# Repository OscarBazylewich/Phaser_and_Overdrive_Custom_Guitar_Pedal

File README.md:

# Phaser and Overdrive Guitar Pedal

This project tries to make better equivalents of guitar pedals that many guitar players use, for example the MXR Phase 90 and the BOSS OD-1. For this, the project uses new methods of analog circuit design and PCB design. For the overdrive, the project also uses some circuit methods from the Ibanez Tube Screamer.

This repository contains these items:

- An LTspice schematic, with the third-party TL072 model that the schematic uses.
- A KiCad project. In this project, the two effects, the power supply and two footswitches are on one 4-layer PCB. The PCB has the correct dimensions for a Hammond 1590BB enclosure.

## Features

- A JFET phaser with four all-pass stages (Rate, Depth). An LFO on the PCB modulates the phaser.
- An overdrive with diode clipping, of the OD-1 and Tube Screamer type (Gain, Tone).
- An input buffer, and one DPDT footswitch for each effect. The signal goes through the phaser first.
- One DC jack supplies the power. The PCB makes the ±4.5 V rails. It also has reverse-polarity protection and surge protection.
- An 85.5 mm × 110.75 mm 4-layer PCB, with TVS protection on the two audio jacks.

## Hardware

### Signal flow

```mermaid
flowchart LR
    IN["Input jack J3"] --> BUF["Input buffer<br/>U5A"]
    BUF --> S1["Phaser footswitch<br/>S1"]
    S1 --> PH["Phaser<br/>4 all-pass stages"]
    S1 -- "phaser off" --> S2["Overdrive footswitch<br/>S2"]
    PH --> S2
    S2 --> OD["Overdrive<br/>gain, clipping, tone"]
    S2 -- "overdrive off" --> OUT["Output jack J2"]
    OD --> OUT
    LFO["Triangle LFO<br/>U5C, U5D"] --> PH
```

### Primary parts

| Part | Function |
| --- | --- |
| U1 TPS560430 buck converter | DC input to +5.5 V |
| U2 LM2662 charge pump | +5.5 V to −5.5 V |
| U3 TPS72301, U4 TPS7E82 LDOs | −4.5 V and +4.5 V rails |
| U5–U7 TL074 quad op-amps | Buffers, LFO, phaser, overdrive |
| Q1–Q4 J113 JFETs | Voltage-controlled resistors in the phaser |
| D1 CUS520 Schottky, D2–D4 20 V TVS | Reverse-polarity, surge and ESD protection |
| D5–D8 1N4148 | Overdrive clipping diodes |
| VR1–VR4 PTV09A potentiometers, RV1/RV2 3386P trimmers | Controls (refer to the next table) |
| S1, S2 SF12011F DPDT footswitches | Phaser and overdrive on/off |
| J1 2.1 × 5.5 mm DC jack, J2/J3 MJ-63022A 6.35 mm jacks | Power, output, input |

### Controls

| Control | Ref | Value | Function |
| --- | --- | --- | --- |
| Rate | VR1 | 1 MΩ linear | LFO frequency |
| Depth | VR2 | 1 MΩ linear | Level of the phase-shifted signal in the mixed output |
| Tone | VR3 | 20 kΩ log | Tone control (active filter) |
| Gain | VR4 | 1 MΩ log | Overdrive feedback resistance |
| LFO offset trimmer | RV1 | 500 kΩ | LFO DC level (J113 bias) |
| LFO hysteresis trimmer | RV2 | 220 kΩ | LFO amplitude and frequency |

## Circuit

The sections that follow use the KiCad reference designators. The LTspice schematic uses different reference designators.

The LTspice schematic has the same topology and the same values as the KiCad schematic, with these differences:

- All the potentiometers are linear.
- The Tone potentiometer is 1 MΩ (KiCad: 20 kΩ).
- The clipping diodes are 1N4007 (KiCad: 1N4148).
- There are no footswitches.
- Ideal ±4.5 V sources supply the power.
- The same input signal goes to the phaser and to the overdrive. The phaser and the overdrive have different outputs.

### Power supply

- The KiCad schematic gives 9–18 V as the range for the DC input. D1 (Schottky, in series) gives reverse-polarity protection. D2 (20 V TVS) sends surges to ground.
- U1 (buck converter) makes +5.5 V. U2 (charge pump) changes this voltage to an unregulated −5.5 V.
- U4 and U3 (LDOs) decrease these voltages to ±4.5 V. Each TL074 has 100 nF decoupling capacitance on each rail.

### Input buffer and footswitches

- C14 (1 µF) connects the tip of the input jack to U5A through AC coupling. U5A is a voltage follower.
- R9 (1 MΩ) sets the input impedance and the DC bias. D4 gives ESD protection on the tip.
- Each footswitch is a DPDT selector. It sends the signal through the effect, or it bypasses the effect.
- NC_1 and NC_2 are connected together. Thus, when an effect is off, the footswitch bypasses that effect.
- When the two effects are off, U5A stays in the signal path.

### LFO

- U5C is a Schmitt trigger. The output of U5C charges and discharges C16 (4.7 µF) through the Rate potentiometer.
- RV2 sets the hysteresis. The LTspice notes give an LFO frequency range of approximately 0.185 Hz to 12.2 Hz.
- U5D amplifies the voltage on C16 and makes the `TriangleOut` signal. `TriangleOut` goes to the gates of all four JFETs (test pad TP3).
- RV1 sets the DC offset of `TriangleOut`. This offset sets the bias of the JFETs. The LTspice notes give a J113 cut-off voltage of −0.5 V to −3.0 V.

### Phaser

- U6A is the phaser buffer. The output of U6A goes to the all-pass stages and to the dry path.
- There are four all-pass stages (U7A–U7D). Each stage has a J113 JFET across a 56 kΩ resistor to ground.
- When the LFO changes the gate voltage, the resistance of the JFET changes. Thus, the phase-shift frequency of the stage also changes.
- U6B adds the phase-shifted signal from the Depth potentiometer to the dry signal. At some frequencies, the two signals are out of phase. At these frequencies, phase cancellation occurs. This phase cancellation makes the notches.
- The LTspice notes show the two notches at 53.5 Hz and 311.9 Hz (R = 56 kΩ, C = 22 nF).
- When current flows through the JFETs, the frequencies of the notches increase. This occurs because the JFETs decrease the total resistance across R.

### Overdrive

- U6C is a non-inverting gain stage. R29 (56 kΩ) plus the Gain potentiometer is the feedback resistance. C28 (82 pF) and two anti-parallel diode pairs (D5–D8) are across this resistance.
- The mid-band gain is approximately 6.6× to 107×. The lower corner frequency of the amplified band is approximately 723 Hz (R30 10 kΩ, C30 22 nF).
- When the signal voltage is more than the total forward voltage of two diodes, current flows through the diodes. The diodes then give soft clipping of the signal in the feedback loop.
- The signal then goes through a passive RC low-pass filter (723 Hz) to the tone stage U6D. The LTspice schematic identifies this tone stage as an active high-pass filter (3.288 kHz at wiper = 1).

## How to start

These items are necessary:

- KiCad 10.0 or a newer version.
- LTspice.
- An LTspice potentiometer model. You must supply this model.

The LTspice schematic loads `potentiometer.sub`. This repository does **not** include this file.

### How to import third-party models into LTspice

1. Download the .sub and .asy files from the `LTSpice/3rdParty/` folder.
2. Put the files in your local LTspice folder:
   - Put the .sub files in the `sub` folder.
   - Put the TL072 .asy file in the `sym/OpAmps/` folder, because the LTspice schematic identifies the op-amp as `OpAmps\TL072`.
   - Put all other .asy files in the `sym` folder.
3. Put the files of your potentiometer model in the folders of step 2.
4. Open `LTSpice/Schematic.asc`.
5. Start the simulation (a 15 s `.tran` with a 100 mV, 100 Hz test tone).
6. Use the probe to show the waveforms of `InputSignal`, `TriangleOut`, `SignalOutPhaser` and `SignalOutOD`.
7. To show the frequency response, do these steps:
   1. Change the `.ac` comment line to a SPICE directive.
   2. Change the `.tran` directive to a comment.
   3. Start the simulation again.

**Note:** When you update LTspice, LTspice can delete the third-party models.

To keep your third-party models, do these steps:

1. Keep a copy of all your third-party .sub and .asy files in a different folder (not in your local LTspice folder).
2. After you update LTspice, manually copy these files into the same folders as in step 2 of "How to import third-party models into LTspice".

### How to import third-party libraries into KiCad

You can open `KiCAD/GuitarPedalV4.kicad_pro` in KiCad 10 without these libraries. This is possible because the KiCad schematic and the PCB file contain all the symbols and footprints. These libraries are necessary only when you edit parts.

1. Extract the two ZIP files in `KiCAD/Libraries/` into a folder that you select.
2. To import the symbols, do these steps:
   1. Open the symbol editor.
   2. Click the **Preferences** menu.
   3. Select **Manage Symbol Libraries**.
   4. Click the folder icon.
   5. Navigate to a folder that contains .kicad_sym files.
   6. Import the .kicad_sym files in this folder.
   7. Keep each file name as its nickname, because the KiCad schematic uses these names.
   8. If other folders contain .kicad_sym files, do steps 4 to 7 again for each of these folders.

   **Note:** The KiCad project uses these .kicad_sym files: the five `1_...` files, `Chassis` (in `Chassis.pretty/`) and `SamacSys_Parts`.
3. To import the footprints, do these steps:
   1. Open the footprint editor.
   2. Click the **Preferences** menu.
   3. Select **Manage Footprint Libraries**.
   4. Click the folder icon.
   5. Add the `Chassis.pretty` and `SamacSys_Parts.pretty` folders. Each footprint library is a folder, not one .kicad_mod file.
4. If KiCad does not show the 3D models of the custom parts, change the paths of these 3D models:
   1. For each footprint of a custom part, navigate to **Footprint Properties > 3D Models**.
   2. Change the path to the related STEP file in the extracted `SamacSys_Parts.3dshapes/` or `Chassis.pretty/3D Files/` folder.

   **Note:** These 3D models use absolute paths on the computer of the designer.

## Repository structure

```text
.
├── KiCAD/
│   ├── GuitarPedalV4.kicad_pro      # KiCad 10 project
│   ├── GuitarPedalV4.kicad_sch      # Root sheet
│   ├── PowerSupply.kicad_sch        # Power supply
│   ├── Analog.kicad_sch             # Buffer, LFO, phaser, footswitches, jacks
│   ├── Overdrive.kicad_sch          # Overdrive sub-sheet
│   ├── GuitarPedalV4.kicad_pcb      # 4-layer PCB
│   └── Libraries/                   # ZIP files of the DIY and SamacSys libraries
├── LTSpice/
│   ├── Schematic.asc                # Full circuit with LTspice notes
│   └── 3rdParty/                    # TL072 model and symbol
├── LICENSE
└── README.md
```

## Simulation examples

## Credits

- Oscar Bazylewich did the circuit design, the simulation and the PCB layout.
- This project uses the MXR Phase 90, the BOSS OD-1 and the Ibanez Tube Screamer as examples.
- TL072 LTspice model: third-party macromodel (`tl072.sub`, from PARTS release 4.01).
- SamacSys supplied the KiCad symbols, footprints and 3D models of the J113, MJ-63022A, PTV09A, 3386P and SF12011F parts.

## License

The license of this project is the GNU General Public License v3.0. Refer to [LICENSE](LICENSE).

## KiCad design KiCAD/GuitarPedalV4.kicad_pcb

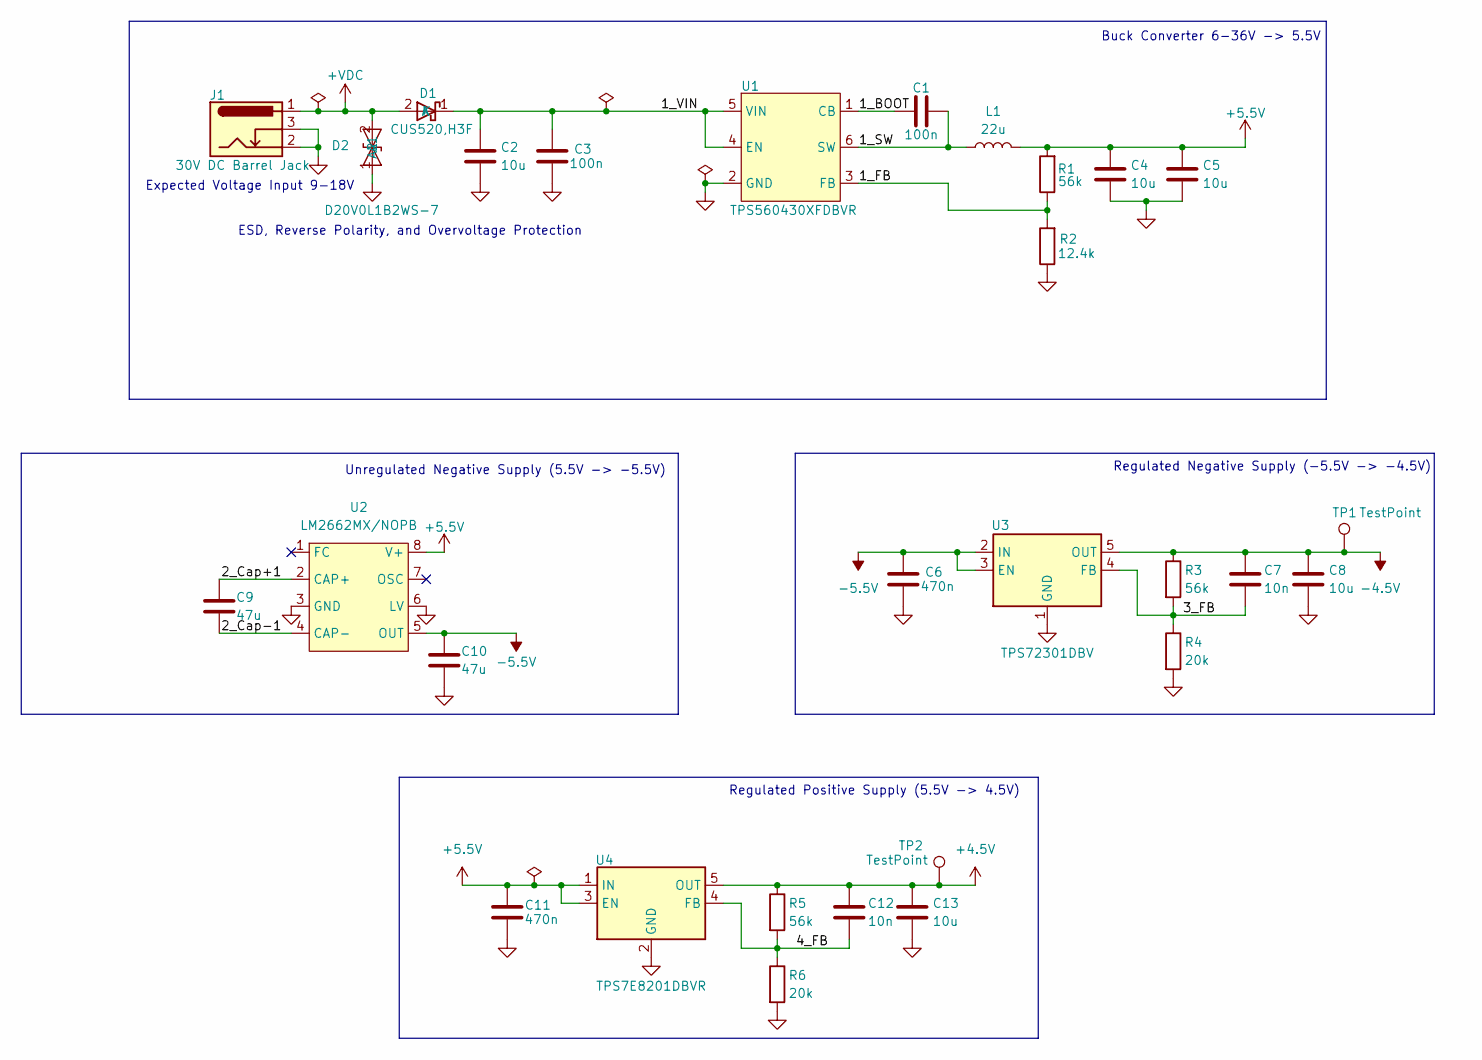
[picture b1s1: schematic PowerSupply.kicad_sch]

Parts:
C1, C3: 100n; C_0603_1608Metric_Pad1.08x0.95mm_HandSolder; Manufacturer Part Number C1608X5R1H104K080AA
C2, C4, C5, C8, C13: 10u; C_0805_2012Metric_Pad1.18x1.45mm_HandSolder; Manufacturer Part Number C2012X5R1H106K125AC
C6, C11: 470n; C_0603_1608Metric_Pad1.08x0.95mm_HandSolder; Manufacturer Part Number CGA3E1X7R1V474K080AC
C7, C12: 10n; C_0603_1608Metric_Pad1.08x0.95mm_HandSolder; Manufacturer Part Number CGA3E2X7R1H103K080AA
C9, C10: 47u; C_1206_3216Metric_Pad1.33x1.80mm_HandSolder; Manufacturer Part Number C3216X5R1E476M160AC
D1: CUS520,H3F; D_SOD-323_HandSoldering; Manufacturer Part Number CUS520,H3F
D2: D20V0L1B2WS-7; D_SOD-323_HandSoldering; Manufacturer Part Number D20V0L1B2WS-7
J1: 30V DC Barrel Jack; BarrelJack_GCT_DCJ200-10-A_Horizontal; Manufacturer Part Number 694106301002
L1: 22u; L_0805_2012Metric_Pad1.05x1.20mm_HandSolder; Manufacturer Part Number MLZ2012P220WTD25
R1, R3, R5: 56k; R_0603_1608Metric_Pad0.98x0.95mm_HandSolder; Manufacturer Part Number CRCW060356K0FKEA
R2: 12.4k; R_0603_1608Metric_Pad0.98x0.95mm_HandSolder; Manufacturer Part Number CRCW060312K4FKEA
R4, R6: 20k; R_0603_1608Metric_Pad0.98x0.95mm_HandSolder; Manufacturer Part Number CRCW060320K0FKEC
TP1, TP2: TestPoint; TestPoint_Pad_1.0x1.0mm
U1: TPS560430XFDBVR; SOT-23-6; Manufacturer Part Number TPS560430XFDBVR
U2: LM2662MX/NOPB; SOIC-8_3.9x4.9mm_P1.27mm; Manufacturer Part Number LM2662MX/NOPB
U3: TPS72301DBV; SOT-23-5_HandSoldering; Manufacturer Part Number TPS72301DBVRG4
U4: TPS7E8201DBVR; SOT-23-5_HandSoldering; Manufacturer Part Number TPS7E8201DBVR

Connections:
+4.5V: C12.1, C13.1, R5.1, TP2.1 (1_1), U4.5 (OUT); also elsewhere on the board
+5.5V: C4.1, C5.1, C11.2, L1.2, R1.2, U2.8 (V+), U4.1 (IN), U4.3 (EN)
+VDC: D1.2 (A), D2.2 (A2), J1.1
-4.5V: C7.1, C8.1, R3.1, TP1.1 (1_1), U3.5 (OUT); also elsewhere on the board
-5.5V: C6.2, C10.1, U2.5 (OUT), U3.2 (IN), U3.3 (EN)
/Power Supply Section/1_BOOT: C1.2, U1.1 (CB)
/Power Supply Section/1_FB: R1.1, R2.2, U1.3 (FB)
/Power Supply Section/1_SW: C1.1, L1.1, U1.6 (SW)
/Power Supply Section/1_VIN: C2.1, C3.2, D1.1 (K), U1.4 (EN), U1.5 (VIN)
/Power Supply Section/2_Cap+1: C9.1, U2.2 (CAP+)
/Power Supply Section/2_Cap-1: C9.2, U2.4 (CAP-)
/Power Supply Section/3_FB: C7.2, R3.2, R4.1, U3.4 (FB)
/Power Supply Section/4_FB: C12.2, R5.2, R6.1, U4.4 (FB)
GND: C2.2, C3.1, C4.2, C5.2, C6.1, C8.2, C10.2, C11.1, C13.2, D2.1 (A1), J1.2, J1.3, R2.1, R4.2, R6.2, U1.2 (GND), U2.3 (GND), U2.6 (LV), U3.1 (GND), U4.2 (GND); also elsewhere on the board

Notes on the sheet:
Regulated Negative Supply (-5.5V -> -4.5V)
ESD, Reverse Polarity, and Overvoltage Protection
Regulated Positive Supply (5.5V -> 4.5V)
Unregulated Negative Supply (5.5V -> -5.5V)
Expected Voltage Input 9-18V
Buck Converter 6-36V -> 5.5V

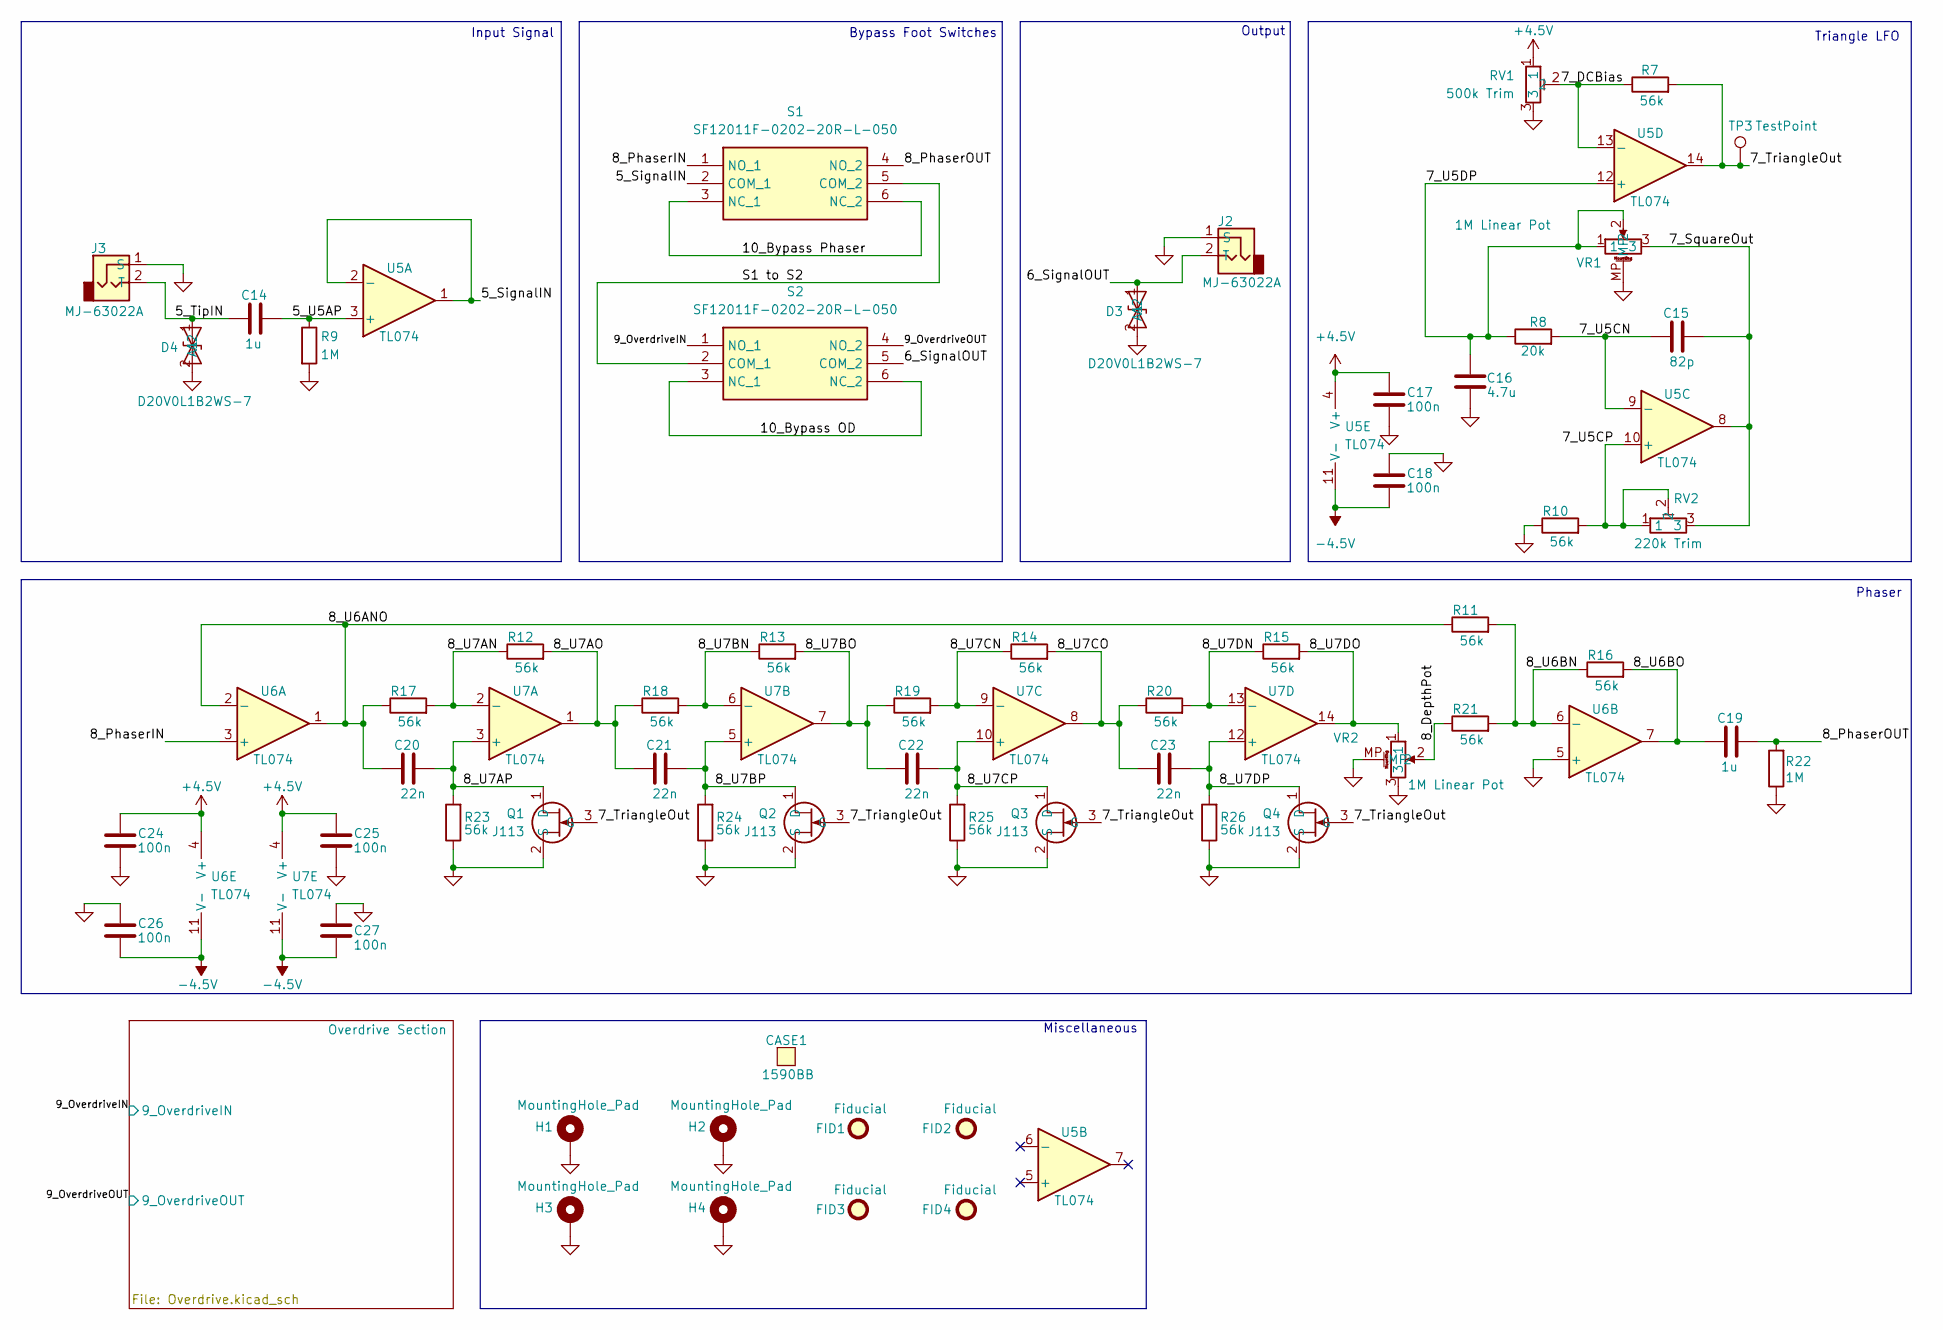
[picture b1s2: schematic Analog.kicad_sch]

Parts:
C14, C19: 1u; C_Rect_L7.2mm_W4.5mm_P5.00mm_FKS2_FKP2_MKS2_MKP2; Manufacturer Part Number B32529C0105J189
C15: 82p; C_Disc_D3.8mm_W2.6mm_P2.50mm; Manufacturer Part Number K820J15C0GF5TL2
C16: 4.7u; C_Rect_L18.0mm_W7.0mm_P15.00mm_FKS3_FKP3; Manufacturer Part Number B32522C0475J000
C17, C18, C24, C25, C26, C27: 100n; C_0603_1608Metric_Pad1.08x0.95mm_HandSolder; Manufacturer Part Number C1608X5R1H104K080AA
C20, C21, C22, C23: 22n; C_Rect_L7.2mm_W2.5mm_P5.00mm_FKS2_FKP2_MKS2_MKP2; Manufacturer Part Number B32529C1223J289
CASE1: 1590BB; Manufacturer Part Number 1590BB
D3, D4: D20V0L1B2WS-7; D_SOD-323_HandSoldering; Manufacturer Part Number D20V0L1B2WS-7
FID1, FID2, FID3, FID4: Fiducial
H1, H2, H3, H4: MountingHole_Pad; MountingHole_3.2mm_M3_Pad
J2, J3: MJ-63022A; MJ63022A; Manufacturer Part Number MJ-63022A
Q1, Q2, Q3, Q4: J113; 2N3904BU; Manufacturer Part Number J113
R7, R10, R11, R12, R13, R14, R15, R16, R17, R18, R19, R20, R21, R23, R24, R25, R26: 56k; R_0603_1608Metric_Pad0.98x0.95mm_HandSolder; Manufacturer Part Number CRCW060356K0FKEA
R8: 20k; R_0603_1608Metric_Pad0.98x0.95mm_HandSolder; Manufacturer Part Number CRCW060320K0FKEC
R9, R22: 1M; R_0603_1608Metric_Pad0.98x0.95mm_HandSolder; Manufacturer Part Number CRCW06031M00FKEA
RV1: 500k Trim; 3386P1504LF; Manufacturer Part Number 3386P-1-504LF
RV2: 220k Trim; 3386P1504LF; Manufacturer Part Number 3386P-1-224LF
S1, S2: SF12011F-0202-20R-L-050; SF12011F020220RM050; Manufacturer Part Number SF12011F-0202-20R-L-050
TP3: TestPoint; TestPoint_Pad_1.0x1.0mm
U5, U6, U7: TL074; SOIC-14_3.9x8.7mm_P1.27mm; Manufacturer Part Number TL074HIDR
VR1, VR2: 1M Linear Pot; PTV09A4025FA105; Manufacturer Part Number PTV09A-4020F-B105

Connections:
+4.5V: C17.2, C24.2, C25.2, RV1.1, U5.4 (V+), U6.4 (V+), U7.4 (V+); also elsewhere on the board
-4.5V: C18.1, C26.1, C27.1, U5.11 (V-), U6.11 (V-), U7.11 (V-); also elsewhere on the board
/Analog Section/5_SignalIN: S1.2 (COM_1), U5.1, U5.2 (-)
/Analog Section/5_TipIN: C14.1, D4.1 (A1), J3.2 (T)
/Analog Section/5_U5AP: C14.2, R9.1, U5.3 (+)
/Analog Section/6_SignalOUT: D3.1 (A1), J2.2 (T), S2.5 (COM_2)
/Analog Section/7_DCBias: R7.1, RV1.2, U5.13 (-)
/Analog Section/7_SquareOut: C15.2, RV2.3, U5.8, VR1.3
/Analog Section/7_TriangleOut: Q1.3 (G), Q2.3 (G), Q3.3 (G), Q4.3 (G), R7.2, TP3.1 (1_1), U5.14
/Analog Section/7_U5CN: C15.1, R8.2, U5.9 (-)
/Analog Section/7_U5CP: R10.2, RV2.1, RV2.2, U5.10 (+)
/Analog Section/7_U5DP: C16.2, R8.1, U5.12 (+), VR1.1, VR1.2
/Analog Section/8_DepthPot: R21.1, VR2.2
/Analog Section/8_PhaserIN: S1.1 (NO_1), U6.3 (+)
/Analog Section/8_PhaserOUT: C19.2, R22.2, S1.4 (NO_2)
/Analog Section/8_U6ANO: C20.1, R11.1, R17.1, U6.1, U6.2 (-)
/Analog Section/8_U6BN: R11.2, R16.1, R21.2, U6.6 (-)
/Analog Section/8_U6BO: C19.1, R16.2, U6.7
/Analog Section/8_U7AN: R12.1, R17.2, U7.2 (-)
/Analog Section/8_U7AO: C21.1, R12.2, R18.1, U7.1
/Analog Section/8_U7AP: C20.2, Q1.1 (D), R23.2, U7.3 (+)
/Analog Section/8_U7BN: R13.1, R18.2, U7.6 (-)
/Analog Section/8_U7BO: C22.1, R13.2, R19.1, U7.7
/Analog Section/8_U7BP: C21.2, Q2.1 (D), R24.2, U7.5 (+)
/Analog Section/8_U7CN: R14.1, R19.2, U7.9 (-)
/Analog Section/8_U7CO: C23.1, R14.2, R20.1, U7.8
/Analog Section/8_U7CP: C22.2, Q3.1 (D), R25.2, U7.10 (+)
/Analog Section/8_U7DN: R15.1, R20.2, U7.13 (-)
/Analog Section/8_U7DO: R15.2, U7.14, VR2.1
/Analog Section/8_U7DP: C23.2, Q4.1 (D), R26.2, U7.12 (+)
/Analog Section/9_OverdriveIN: S2.1 (NO_1); also elsewhere on the board
/Analog Section/9_OverdriveOUT: S2.4 (NO_2); also elsewhere on the board
/Analog Section/10_Bypass OD: S2.3 (NC_1), S2.6 (NC_2)
/Analog Section/10_Bypass Phaser: S1.3 (NC_1), S1.6 (NC_2)
/Analog Section/S1 to S2: S1.5 (COM_2), S2.2 (COM_1)
GND: C16.1, C17.1, C18.2, C24.1, C25.1, C26.2, C27.2, D3.2 (A2), D4.2 (A2), H1.1 (1_1), H2.1 (1_1), H3.1 (1_1), H4.1 (1_1), J2.1 (S), J3.1 (S), Q1.2 (S), Q2.2 (S), Q3.2 (S), Q4.2 (S), R9.2, R10.1, R22.1, R23.1, R24.1, R25.1, R26.1, RV1.3, U6.5 (+), VR1.MP, VR2.3, VR2.MP; also elsewhere on the board

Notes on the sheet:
Phaser
Miscellaneous
Output
Bypass Foot Switches
Input Signal
Triangle LFO

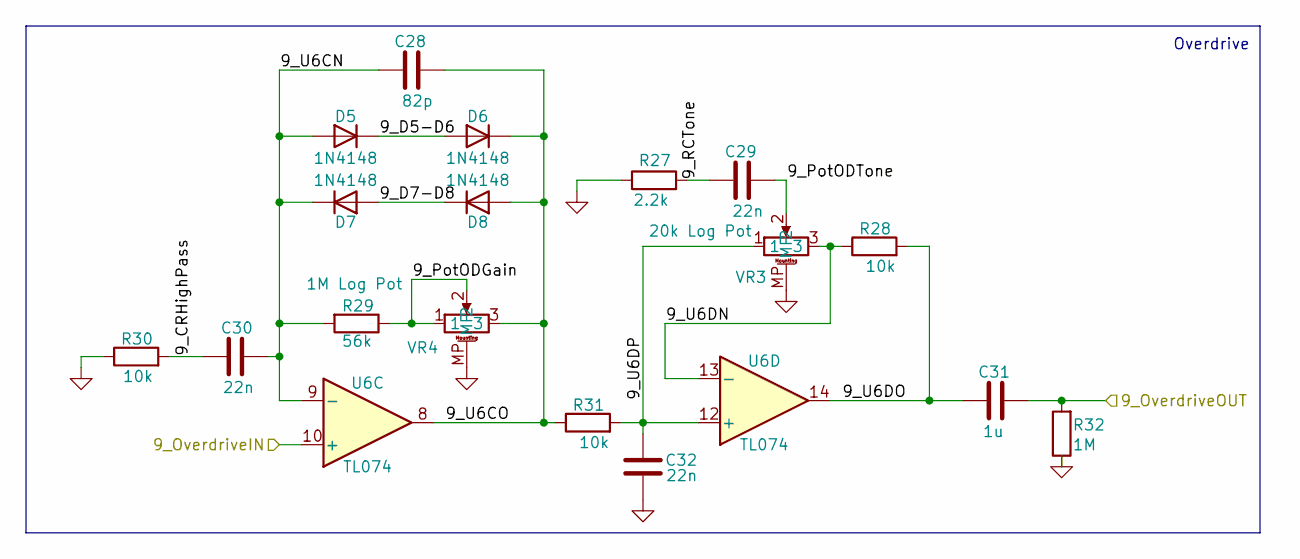
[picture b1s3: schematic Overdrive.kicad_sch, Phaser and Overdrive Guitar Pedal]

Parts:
C28: 82p; C_Disc_D3.8mm_W2.6mm_P2.50mm; Manufacturer Part Number K820J15C0GF5TL2
C29, C30, C32: 22n; C_Rect_L7.2mm_W2.5mm_P5.00mm_FKS2_FKP2_MKS2_MKP2; Manufacturer Part Number B32529C1223J289
C31: 1u; C_Rect_L7.2mm_W4.5mm_P5.00mm_FKS2_FKP2_MKS2_MKP2; Manufacturer Part Number B32529C0105J189
D5, D6, D7, D8: 1N4148; D_DO-35_SOD27_P7.62mm_Horizontal; Manufacturer Part Number 1N4148
R27: 2.2k; R_0603_1608Metric_Pad0.98x0.95mm_HandSolder; Manufacturer Part Number CRCW06032K20FKEA
R28, R30, R31: 10k; R_0603_1608Metric_Pad0.98x0.95mm_HandSolder; Manufacturer Part Number CRCW060310K0FKEA
R29: 56k; R_0603_1608Metric_Pad0.98x0.95mm_HandSolder; Manufacturer Part Number CRCW060356K0FKEA
R32: 1M; R_0603_1608Metric_Pad0.98x0.95mm_HandSolder; Manufacturer Part Number CRCW06031M00FKEA
U6: TL074; SOIC-14_3.9x8.7mm_P1.27mm; Manufacturer Part Number TL074HIDR
VR3: 20k Log Pot; PTV09A4025FA105; Manufacturer Part Number PTV09A-4025F-A203
VR4: 1M Log Pot; PTV09A4025FA105; Manufacturer Part Number PTV09A-4025F-A105

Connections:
/Analog Section/9_OverdriveIN: U6.10 (+); also elsewhere on the board
/Analog Section/9_OverdriveOUT: C31.2, R32.2; also elsewhere on the board
/Analog Section/Overdrive Section/9_CRHighPass: C30.2, R30.2
/Analog Section/Overdrive Section/9_D5-D6: D5.1 (K), D6.2 (A)
/Analog Section/Overdrive Section/9_D7-D8: D7.2 (A), D8.1 (K)
/Analog Section/Overdrive Section/9_PotODGain: R29.1, VR4.1, VR4.2
/Analog Section/Overdrive Section/9_PotODTone: C29.2, VR3.2
/Analog Section/Overdrive Section/9_RCTone: C29.1, R27.2
/Analog Section/Overdrive Section/9_U6CN: C28.1, C30.1, D5.2 (A), D7.1 (K), R29.2, U6.9 (-)
/Analog Section/Overdrive Section/9_U6CO: C28.2, D6.1 (K), D8.2 (A), R31.1, U6.8, VR4.3
/Analog Section/Overdrive Section/9_U6DN: R28.1, U6.13 (-), VR3.3
/Analog Section/Overdrive Section/9_U6DO: C31.1, R28.2, U6.14
/Analog Section/Overdrive Section/9_U6DP: C32.2, R31.2, U6.12 (+), VR3.1
GND: C32.1, R27.1, R30.1, R32.1, VR3.MP, VR4.MP; also elsewhere on the board

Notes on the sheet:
Overdrive

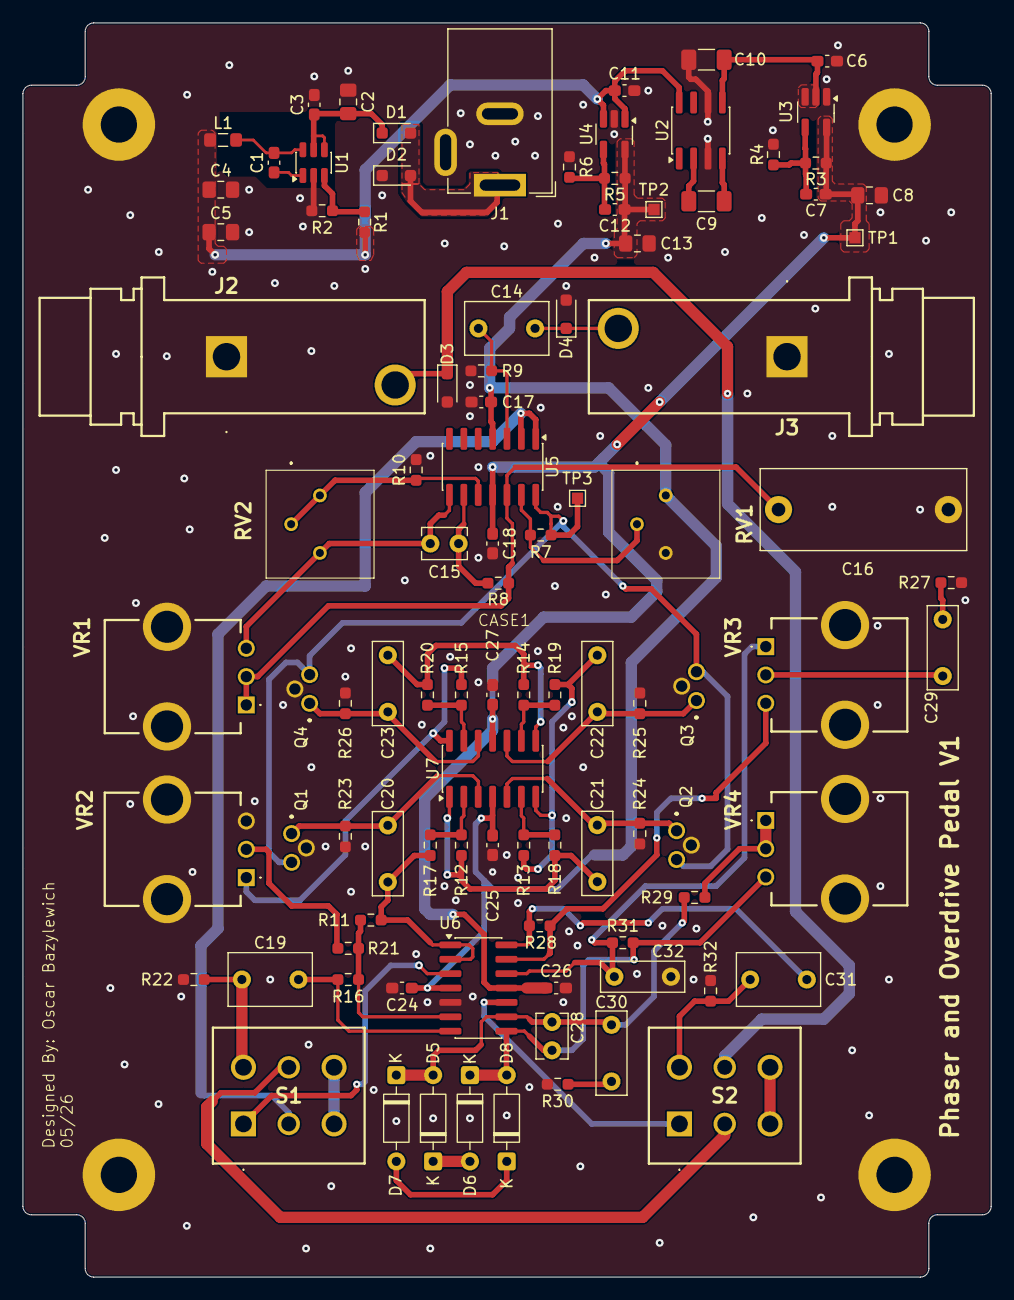
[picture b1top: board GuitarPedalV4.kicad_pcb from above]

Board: 4 copper layers, 85.5 x 110.8 mm, 103 parts (0 on the bottom side), 58 nets.

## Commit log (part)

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2026-05-14 Create a

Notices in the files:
README.md:
License: GPL-3.0
